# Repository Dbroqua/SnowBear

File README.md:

# SnowBear
My personal mechanical keyboard

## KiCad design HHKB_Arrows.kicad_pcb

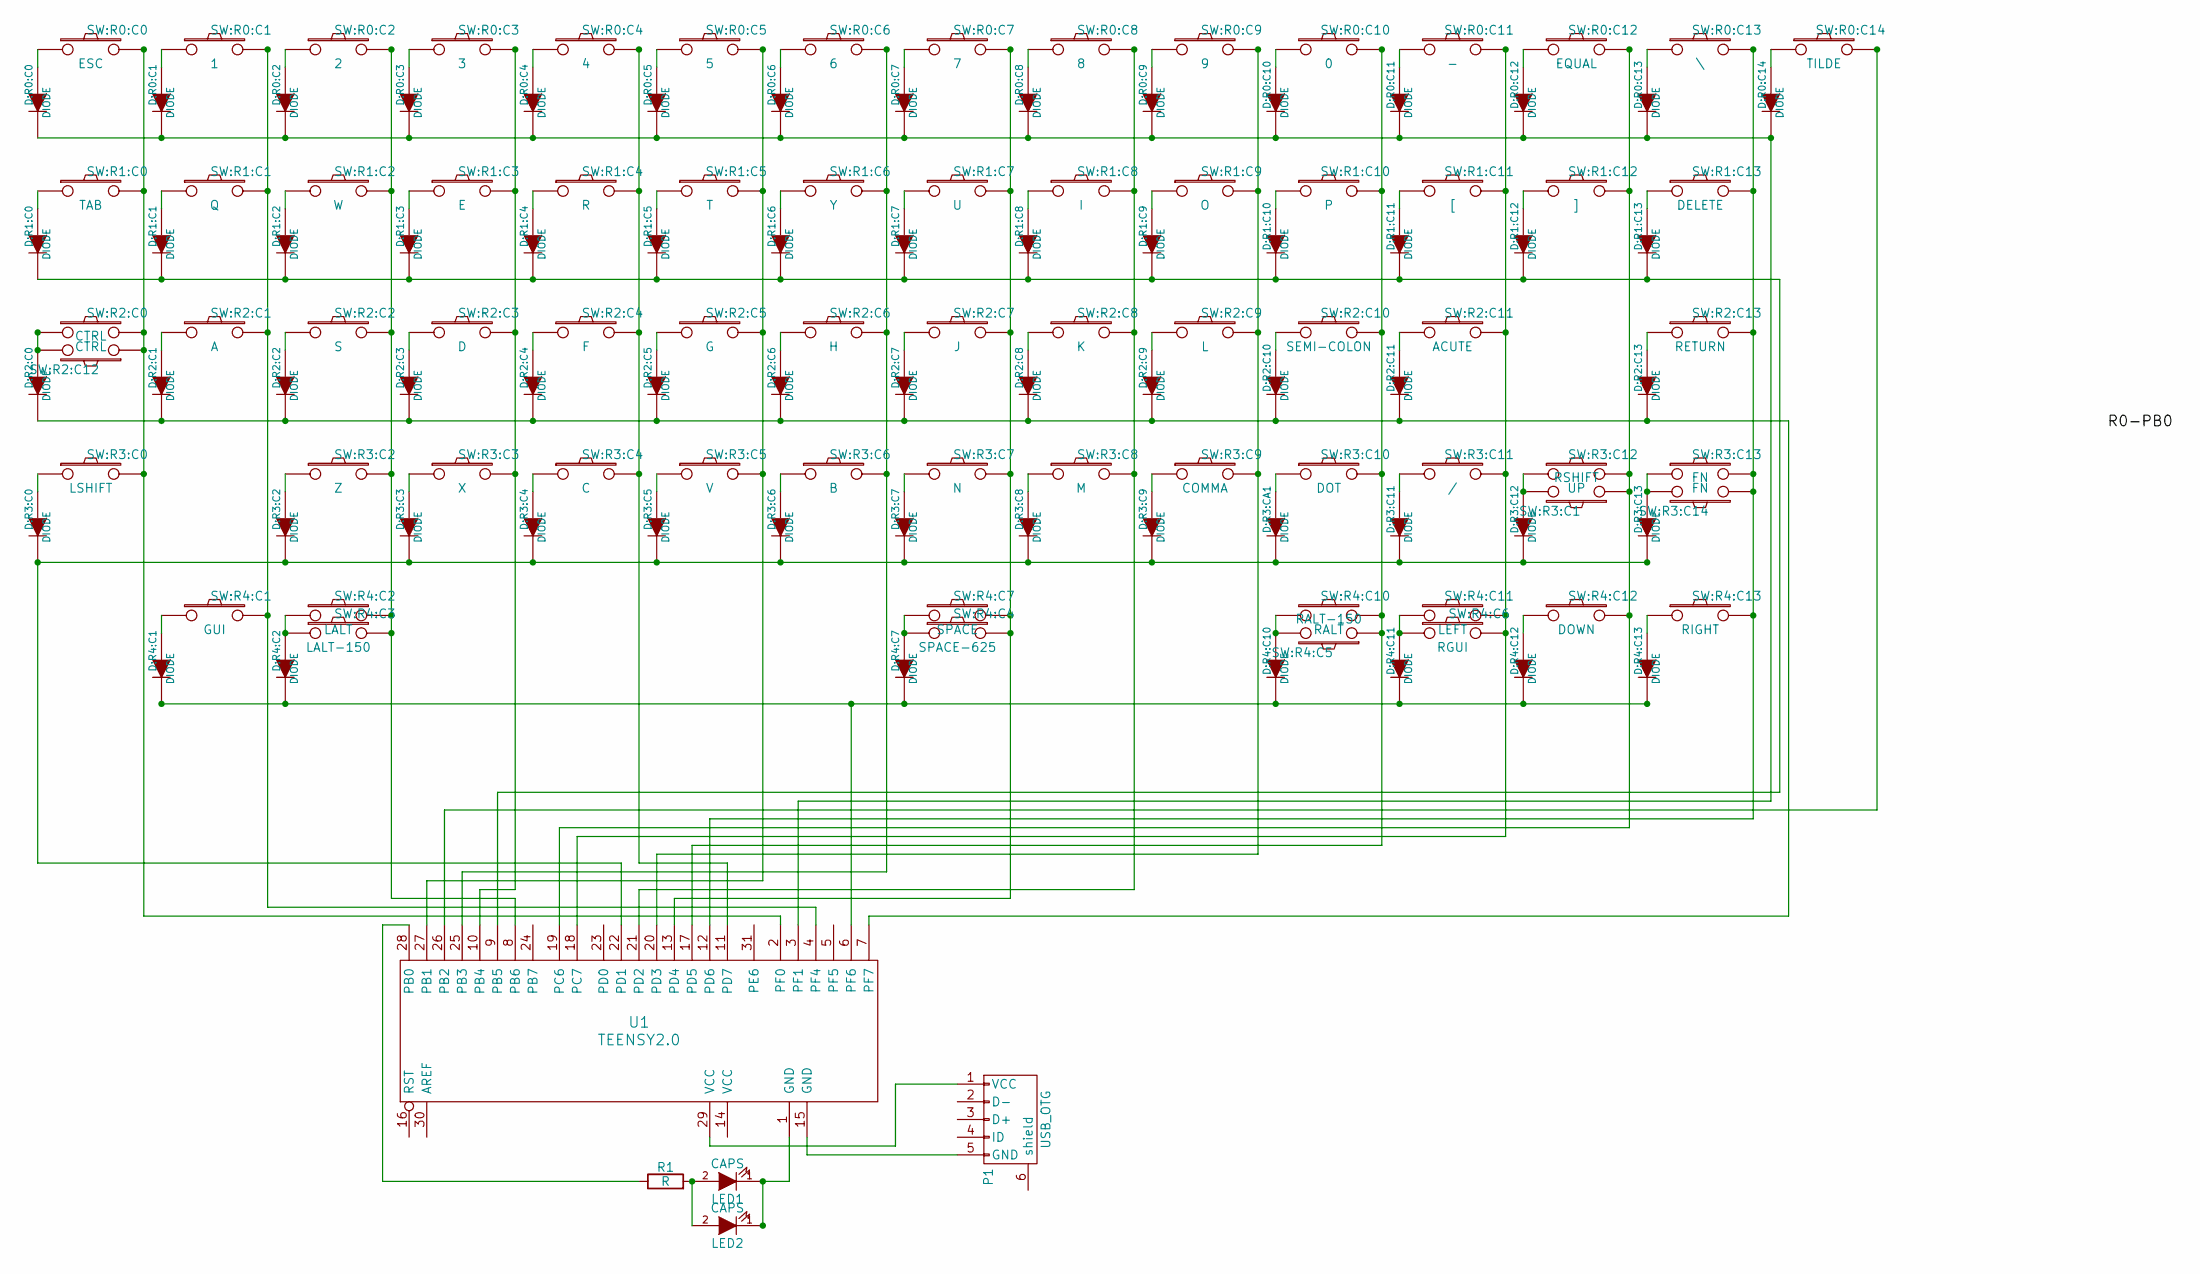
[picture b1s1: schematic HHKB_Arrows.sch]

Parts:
D:R0:C0, D:R0:C1, D:R0:C2, D:R0:C3, D:R0:C4, D:R0:C5, D:R0:C6, D:R0:C7, D:R0:C8: DIODE; SMB_Standard
D:R0:C9, D:R0:C10, D:R0:C11, D:R0:C12, D:R0:C13, D:R0:C14, D:R1:C0, D:R1:C1, D:R1:C2, D:R1:C3, D:R1:C4, D:R1:C5, D:R1:C6, D:R1:C7, D:R1:C8, D:R1:C9, D:R1:C10, D:R1:C11, D:R1:C12, D:R1:C13, D:R2:C0, D:R2:C1, D:R2:C2, D:R2:C3, D:R2:C4, D:R2:C5, D:R2:C6, D:R2:C7, D:R2:C8, D:R2:C9, D:R2:C10, D:R2:C11, D:R2:C13, D:R3:C0, D:R3:C2, D:R3:C3, D:R3:C4, D:R3:C5, D:R3:C6, D:R3:C7, D:R3:C8, D:R3:C9, D:R3:C11, D:R3:C12, D:R3:C13, D:R3:CA1, D:R4:C1, D:R4:C2, D:R4:C7, D:R4:C10, D:R4:C11, D:R4:C12, D:R4:C13: DIODE; SMA_Standard
LED1, LED2: CAPS; CHERRY_MX_LED
P1: USB_OTG; USB_Mini-B
R1: R; RESISTOR
SW:R0:C0: ESC; CHERRY_PCB_100H
SW:R0:C1: 1; CHERRY_PCB_100H
SW:R0:C2: 2; CHERRY_PCB_100H
SW:R0:C3: 3; CHERRY_PCB_100H
SW:R0:C4: 4; CHERRY_PCB_100H
SW:R0:C5: 5; CHERRY_PCB_100H
SW:R0:C6: 6; CHERRY_PCB_100H
SW:R0:C7: 7; CHERRY_PCB_100H
SW:R0:C8: 8; CHERRY_PCB_100H
SW:R0:C9: 9; CHERRY_PCB_100H
SW:R0:C10: 0; CHERRY_PCB_100H
SW:R0:C11: -; CHERRY_PCB_100H
SW:R0:C12: EQUAL; CHERRY_PCB_100H
SW:R0:C13: \\; CHERRY_PCB_100H
SW:R0:C14: TILDE; CHERRY_PCB_100H
SW:R1:C0: TAB; CHERRY_PCB_150H
SW:R1:C1: Q; CHERRY_PCB_100H
SW:R1:C2: W; CHERRY_PCB_100H
SW:R1:C3: E; CHERRY_PCB_100H
SW:R1:C4: R; CHERRY_PCB_100H
SW:R1:C5: T; CHERRY_PCB_100H
SW:R1:C6: Y; CHERRY_PCB_100H
SW:R1:C7: U; CHERRY_PCB_100H
SW:R1:C8: I; CHERRY_PCB_100H
SW:R1:C9: O; CHERRY_PCB_100H
SW:R1:C10: P; CHERRY_PCB_100H
SW:R1:C11: [; CHERRY_PCB_100H
SW:R1:C12: ]; CHERRY_PCB_100H
SW:R1:C13: DELETE; CHERRY_PCB_150H
SW:R2:C0: CTRL; CHERRY_PCB_175STEP
SW:R2:C1: A; CHERRY_PCB_100H
SW:R2:C2: S; CHERRY_PCB_100H
SW:R2:C3: D; CHERRY_PCB_100H
SW:R2:C4: F; CHERRY_PCB_100H
SW:R2:C5: G; CHERRY_PCB_100H
SW:R2:C6: H; CHERRY_PCB_100H
SW:R2:C7: J; CHERRY_PCB_100H
SW:R2:C8: K; CHERRY_PCB_100H
SW:R2:C9: L; CHERRY_PCB_100H
SW:R2:C10: SEMI-COLON; CHERRY_PCB_100H
SW:R2:C11: ACUTE; CHERRY_PCB_100H
SW:R2:C12: CTRL; CHERRY_PLATE_175H
SW:R2:C13: RETURN; CHERRY_PCB_225H
SW:R3:C0: LSHIFT; CHERRY_PCB_225H
SW:R3:C1: RSHIFT; CHERRY_PCB_175H
SW:R3:C2: Z; CHERRY_PCB_100H
SW:R3:C3: X; CHERRY_PCB_100H
SW:R3:C4: C; CHERRY_PCB_100H
SW:R3:C5: V; CHERRY_PCB_100H
SW:R3:C6: B; CHERRY_PCB_100H
SW:R3:C7: N; CHERRY_PCB_100H
SW:R3:C8: M; CHERRY_PCB_100H
SW:R3:C9: COMMA; CHERRY_PCB_100H
SW:R3:C10: DOT; CHERRY_PCB_100H
SW:R3:C11: /; CHERRY_PCB_100H
SW:R3:C12: UP; CHERRY_PCB_100H
SW:R3:C13: FN; CHERRY_PCB_175H
SW:R3:C14: FN; CHERRY_PCB_100H
SW:R4:C1: GUI; CHERRY_PCB_100H
SW:R4:C2: LALT; CHERRY_PCB_125H
SW:R4:C3: LALT-150; CHERRY_PCB_150H
SW:R4:C4: SPACE-625; CHERRY_PLATE_625H
SW:R4:C5: RALT-150; CHERRY_PLATE_150H
SW:R4:C6: RGUI; CHERRY_PLATE_100H
SW:R4:C7: SPACE; CHERRY_PLATE_600H
SW:R4:C10: RALT; CHERRY_PLATE_125H
SW:R4:C11: LEFT; CHERRY_PLATE_100H
SW:R4:C12: DOWN; CHERRY_PLATE_100H
SW:R4:C13: RIGHT; CHERRY_PLATE_100H
U1: TEENSY2.0; TEENSY_2.0

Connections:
unnamed: D:R0:C0.1 (A), SW:R0:C0.1
unnamed: D:R0:C0.2 (K), D:R0:C1.2 (K), D:R0:C2.2 (K), D:R0:C3.2 (K), D:R0:C4.2 (K), D:R0:C5.2 (K), D:R0:C6.2 (K), D:R0:C7.2 (K), D:R0:C8.2 (K), D:R0:C9.2 (K), D:R0:C10.2 (K), D:R0:C11.2 (K), D:R0:C12.2 (K), D:R0:C13.2 (K), D:R0:C14.2 (K), U1.3 (PF1)
unnamed: D:R0:C1.1 (A), SW:R0:C1.1
unnamed: D:R0:C2.1 (A), SW:R0:C2.1
unnamed: D:R0:C3.1 (A), SW:R0:C3.1
unnamed: D:R0:C4.1 (A), SW:R0:C4.1
unnamed: D:R0:C5.1 (A), SW:R0:C5.1
unnamed: D:R0:C6.1 (A), SW:R0:C6.1
unnamed: D:R0:C7.1 (A), SW:R0:C7.1
unnamed: D:R0:C8.1 (A), SW:R0:C8.1
unnamed: D:R0:C9.1 (A), SW:R0:C9.1
unnamed: D:R0:C10.1 (A), SW:R0:C10.1
unnamed: D:R0:C11.1 (A), SW:R0:C11.1
unnamed: D:R0:C12.1 (A), SW:R0:C12.1
unnamed: D:R0:C13.1 (A), SW:R0:C13.1
unnamed: D:R0:C14.1 (A), SW:R0:C14.1
unnamed: D:R1:C0.1 (A), SW:R1:C0.1
unnamed: D:R1:C0.2 (K), D:R1:C1.2 (K), D:R1:C2.2 (K), D:R1:C3.2 (K), D:R1:C4.2 (K), D:R1:C5.2 (K), D:R1:C6.2 (K), D:R1:C7.2 (K), D:R1:C8.2 (K), D:R1:C9.2 (K), D:R1:C10.2 (K), D:R1:C11.2 (K), D:R1:C12.2 (K), D:R1:C13.2 (K), U1.9 (PB5)
unnamed: D:R1:C1.1 (A), SW:R1:C1.1
unnamed: D:R1:C2.1 (A), SW:R1:C2.1
unnamed: D:R1:C3.1 (A), SW:R1:C3.1
unnamed: D:R1:C4.1 (A), SW:R1:C4.1
unnamed: D:R1:C5.1 (A), SW:R1:C5.1
unnamed: D:R1:C6.1 (A), SW:R1:C6.1
unnamed: D:R1:C7.1 (A), SW:R1:C7.1
unnamed: D:R1:C8.1 (A), SW:R1:C8.1
unnamed: D:R1:C9.1 (A), SW:R1:C9.1
unnamed: D:R1:C10.1 (A), SW:R1:C10.1
unnamed: D:R1:C11.1 (A), SW:R1:C11.1
unnamed: D:R1:C12.1 (A), SW:R1:C12.1
unnamed: D:R1:C13.1 (A), SW:R1:C13.1
unnamed: D:R2:C0.1 (A), SW:R2:C0.1, SW:R2:C12.2
unnamed: D:R2:C0.2 (K), D:R2:C1.2 (K), D:R2:C2.2 (K), D:R2:C3.2 (K), D:R2:C4.2 (K), D:R2:C5.2 (K), D:R2:C6.2 (K), D:R2:C7.2 (K), D:R2:C8.2 (K), D:R2:C9.2 (K), D:R2:C10.2 (K), D:R2:C11.2 (K), D:R2:C13.2 (K), U1.7 (PF7)
unnamed: D:R2:C1.1 (A), SW:R2:C1.1
unnamed: D:R2:C2.1 (A), SW:R2:C2.1
unnamed: D:R2:C3.1 (A), SW:R2:C3.1
unnamed: D:R2:C4.1 (A), SW:R2:C4.1
unnamed: D:R2:C5.1 (A), SW:R2:C5.1
unnamed: D:R2:C6.1 (A), SW:R2:C6.1
unnamed: D:R2:C7.1 (A), SW:R2:C7.1
unnamed: D:R2:C8.1 (A), SW:R2:C8.1
unnamed: D:R2:C9.1 (A), SW:R2:C9.1
unnamed: D:R2:C10.1 (A), SW:R2:C10.1
unnamed: D:R2:C11.1 (A), SW:R2:C11.1
unnamed: D:R2:C13.1 (A), SW:R2:C13.1
unnamed: D:R3:C0.1 (A), SW:R3:C0.1
unnamed: D:R3:C0.2 (K), D:R3:C2.2 (K), D:R3:C3.2 (K), D:R3:C4.2 (K), D:R3:C5.2 (K), D:R3:C6.2 (K), D:R3:C7.2 (K), D:R3:C8.2 (K), D:R3:C9.2 (K), D:R3:C11.2 (K), D:R3:C12.2 (K), D:R3:C13.2 (K), D:R3:CA1.2 (K), U1.22 (PD1)
unnamed: D:R3:C2.1 (A), SW:R3:C2.1
unnamed: D:R3:C3.1 (A), SW:R3:C3.1
unnamed: D:R3:C4.1 (A), SW:R3:C4.1
unnamed: D:R3:C5.1 (A), SW:R3:C5.1
unnamed: D:R3:C6.1 (A), SW:R3:C6.1
unnamed: D:R3:C7.1 (A), SW:R3:C7.1
unnamed: D:R3:C8.1 (A), SW:R3:C8.1
unnamed: D:R3:C9.1 (A), SW:R3:C9.1
unnamed: D:R3:C11.1 (A), SW:R3:C11.1
unnamed: D:R3:C12.1 (A), SW:R3:C1.2, SW:R3:C12.1
unnamed: D:R3:C13.1 (A), SW:R3:C13.1, SW:R3:C14.2
unnamed: D:R3:CA1.1 (A), SW:R3:C10.1
unnamed: D:R4:C1.1 (A), SW:R4:C1.1
unnamed: D:R4:C1.2 (K), D:R4:C2.2 (K), D:R4:C7.2 (K), D:R4:C10.2 (K), D:R4:C11.2 (K), D:R4:C12.2 (K), D:R4:C13.2 (K), U1.6 (PF6)
unnamed: D:R4:C2.1 (A), SW:R4:C2.1, SW:R4:C3.1
unnamed: D:R4:C7.1 (A), SW:R4:C4.1, SW:R4:C7.1
unnamed: D:R4:C10.1 (A), SW:R4:C5.2, SW:R4:C10.1
unnamed: D:R4:C11.1 (A), SW:R4:C6.1, SW:R4:C11.1
unnamed: D:R4:C12.1 (A), SW:R4:C12.1
unnamed: D:R4:C13.1 (A), SW:R4:C13.1
unnamed: LED1.1 (K), LED2.1 (K), U1.1 (GND)
unnamed: LED1.2 (A), LED2.2 (A), R1.2
unnamed: P1.1 (VCC), U1.29 (VCC)
unnamed: P1.5 (GND), U1.15 (GND)
unnamed: R1.1, U1.28 (PB0)
unnamed: SW:R0:C0.2, SW:R1:C0.2, SW:R2:C0.2, SW:R2:C12.1, SW:R3:C0.2, U1.2 (PF0)
unnamed: SW:R0:C1.2, SW:R1:C1.2, SW:R2:C1.2, SW:R4:C1.2, U1.4 (PF4)
unnamed: SW:R0:C2.2, SW:R1:C2.2, SW:R2:C2.2, SW:R3:C2.2, SW:R4:C2.2, SW:R4:C3.2, U1.8 (PB6)
unnamed: SW:R0:C3.2, SW:R1:C3.2, SW:R2:C3.2, SW:R3:C3.2, U1.10 (PB4)
unnamed: SW:R0:C4.2, SW:R1:C4.2, SW:R2:C4.2, SW:R3:C4.2, U1.11 (PD7)
unnamed: SW:R0:C5.2, SW:R1:C5.2, SW:R2:C5.2, SW:R3:C5.2, U1.27 (PB1)
unnamed: SW:R0:C6.2, SW:R1:C6.2, SW:R2:C6.2, SW:R3:C6.2, U1.25 (PB3)
unnamed: SW:R0:C7.2, SW:R1:C7.2, SW:R2:C7.2, SW:R3:C7.2, SW:R4:C4.2, SW:R4:C7.2, U1.13 (PD4)
unnamed: SW:R0:C8.2, SW:R1:C8.2, SW:R2:C8.2, SW:R3:C8.2, U1.21 (PD2)
unnamed: SW:R0:C9.2, SW:R1:C9.2, SW:R2:C9.2, SW:R3:C9.2, U1.20 (PD3)
unnamed: SW:R0:C10.2, SW:R1:C10.2, SW:R2:C10.2, SW:R3:C10.2, SW:R4:C5.1, SW:R4:C10.2, U1.17 (PD5)
unnamed: SW:R0:C11.2, SW:R1:C11.2, SW:R2:C11.2, SW:R3:C11.2, SW:R4:C6.2, SW:R4:C11.2, U1.18 (PC7)
unnamed: SW:R0:C12.2, SW:R1:C12.2, SW:R3:C1.1, SW:R3:C12.2, SW:R4:C12.2, U1.19 (PC6)
unnamed: SW:R0:C13.2, SW:R1:C13.2, SW:R2:C13.2, SW:R3:C13.2, SW:R3:C14.1, SW:R4:C13.2, U1.12 (PD6)
unnamed: SW:R0:C14.2, U1.26 (PB2)

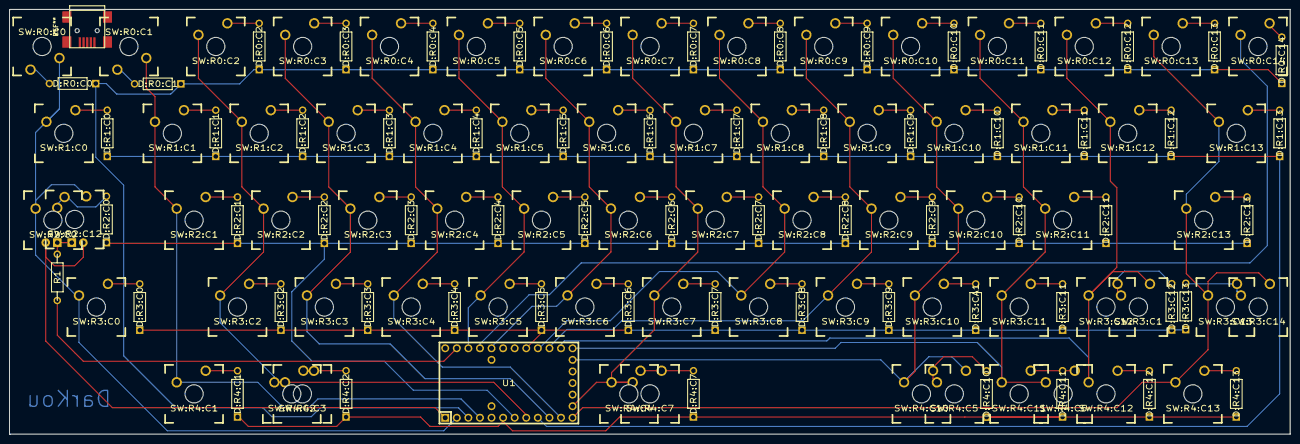
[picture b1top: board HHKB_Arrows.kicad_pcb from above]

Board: 2 copper layers, 281.0 x 93.2 mm, 135 parts (0 on the bottom side), 85 nets.

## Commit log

2016-12-27 - Initial commit for rev1
